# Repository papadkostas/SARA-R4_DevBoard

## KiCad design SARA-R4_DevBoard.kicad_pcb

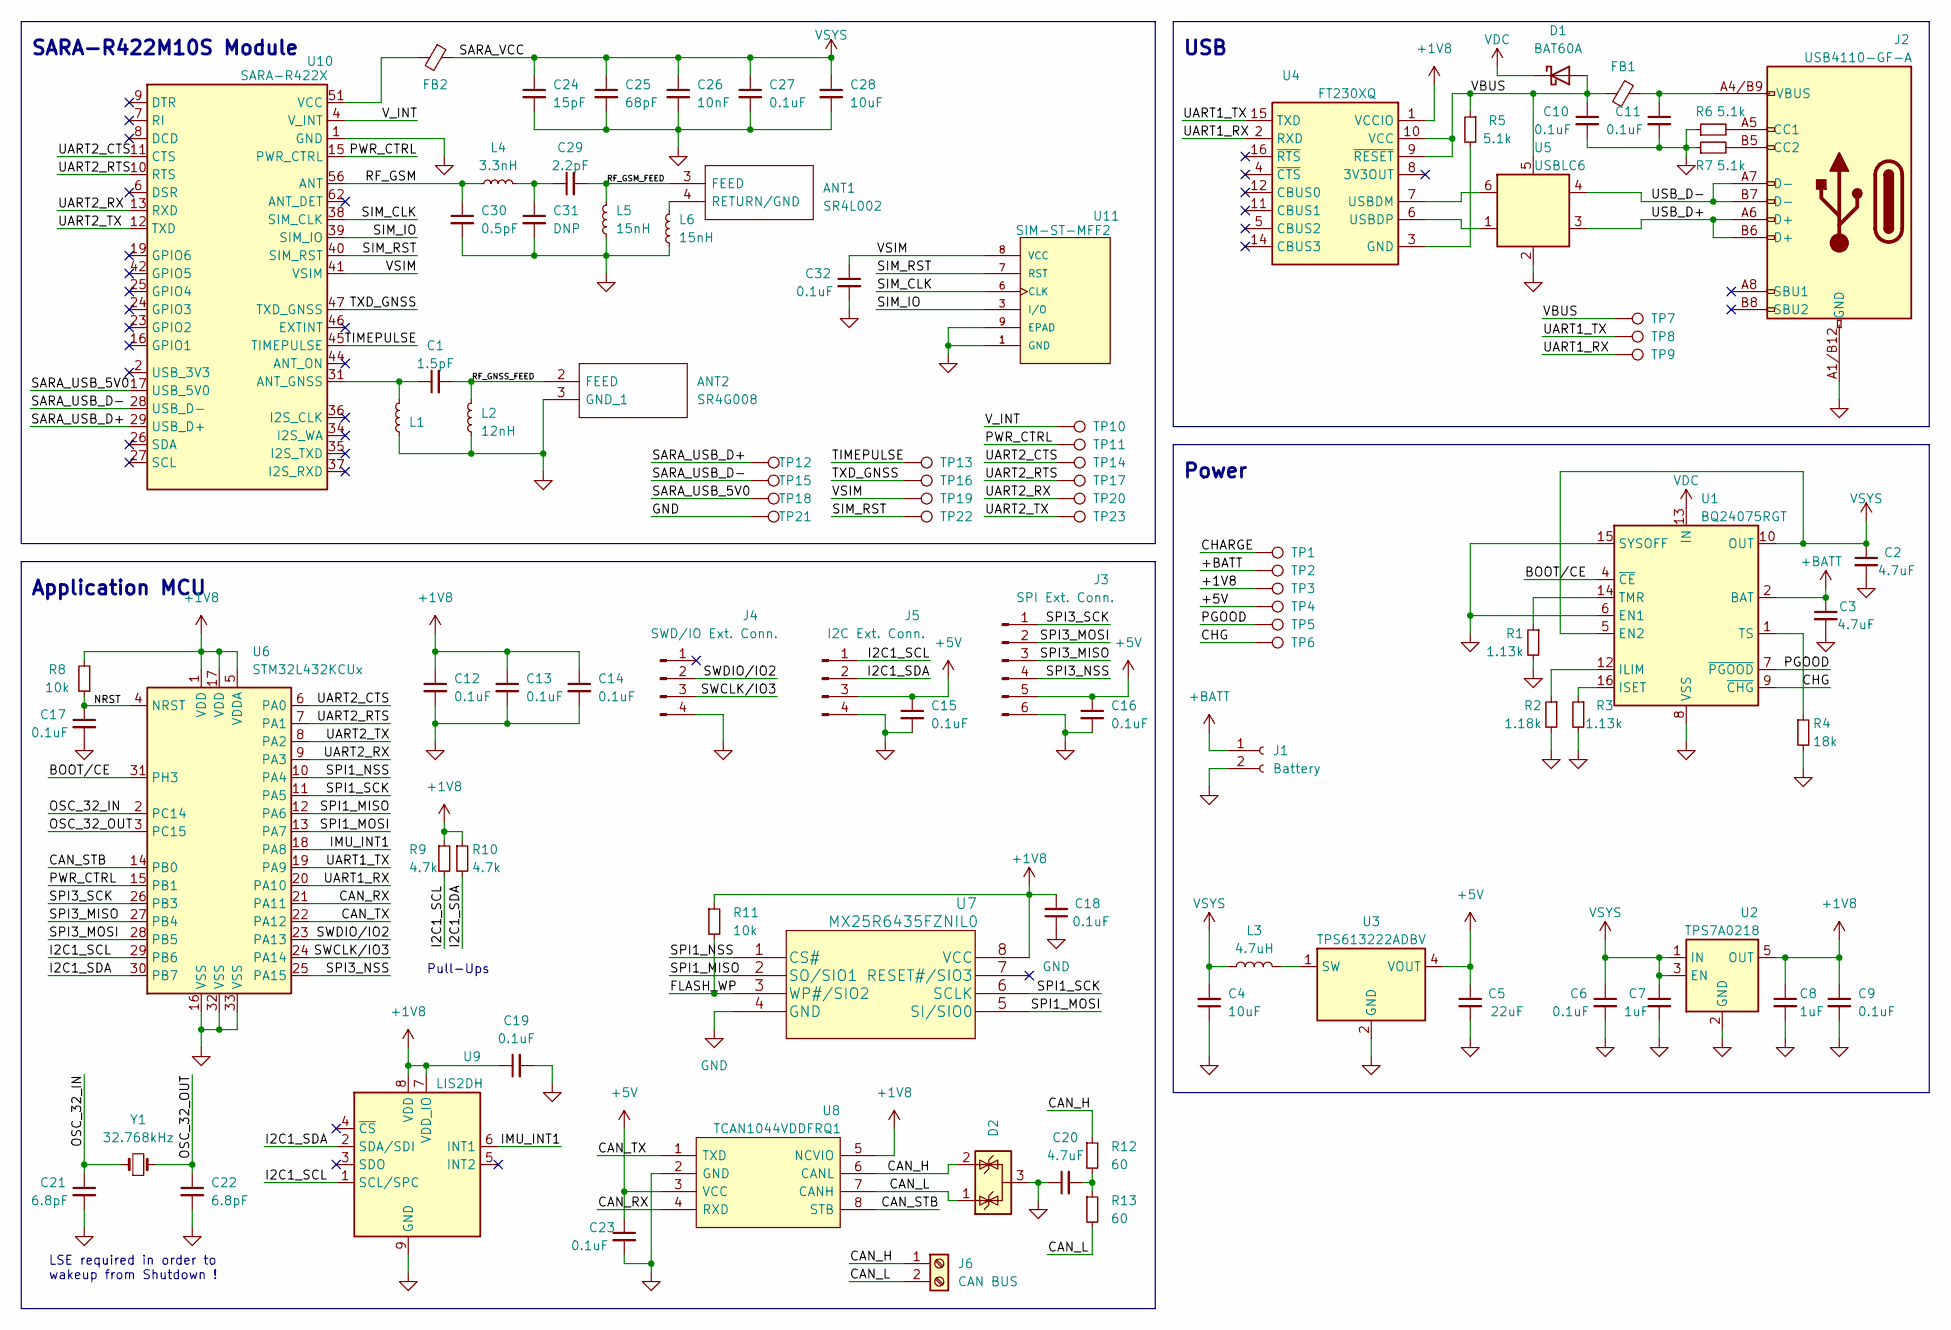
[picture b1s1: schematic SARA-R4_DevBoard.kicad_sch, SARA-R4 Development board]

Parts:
ANT1: SR4L002; Manufacturer_Part_Number SR4L002; Mouser Part Number 237-SR4L002
ANT2: SR4G008; Manufacturer_Part_Number SR4G008; Mouser Part Number 237-SR4G008
C1: 1.5pF; C_0402_1005Metric
C2, C3, C20: 4.7uF; C_0402_1005Metric
C4: 10uF; C_0402_1005Metric
C5: 22uF; C_0402_1005Metric
C6, C9, C10, C11, C12, C13, C14, C15, C16, C17, C18, C19, C23: 0.1uF; C_0402_1005Metric
C7, C8: 1uF; C_0402_1005Metric
C21, C22: 6.8pF; C_0402_1005Metric
C24: 15pF; C_0402_1005Metric; Part GRM1555C1H150J
C25: 68pF; C_0402_1005Metric; Part GRM1555C1H680J
C26: 10nF; C_0402_1005Metric; Part GRM155R71C103K
C27, C32: 0.1uF; C_0402_1005Metric; Part GRM155R61C104K
C28: 10uF; C_0402_1005Metric; Part T520B107M006ATE015
C29: 2.2pF; C_0402_1005Metric
C30: 0.5pF; C_0402_1005Metric
C31: DNP; C_0402_1005Metric
D1: BAT60A; D_SOD-323
D2: SZNUP2115LT1G; SOT-23
FB1: USB_Bead; L_0603_1608Metric
FB2: FerriteBead_Small; L_0603_1608Metric; Part BLM18EG221SN1
J1: Battery; JST_PH_S2B-PH-SM4-TB_1x02-1MP_P2.00mm_Horizontal
J2: USB4110-GF-A; GCT_USB4110-GF-A_REVB; Manufacturer_Part_Number USB4110-GF-A; Mouser Part Number 640-USB4110-GF-A
J3: SPI Ext. Conn.; JST_SH_SM06B-SRSS-TB_1x06-1MP_P1.00mm_Horizontal
J4: SWD/IO Ext. Conn.; JST_SH_SM04B-SRSS-TB_1x04-1MP_P1.00mm_Horizontal
J5: I2C Ext. Conn.; JST_SH_SM04B-SRSS-TB_1x04-1MP_P1.00mm_Horizontal
J6: CAN BUS; C_0603_1608Metric
L1: L_Small; L_0402_1005Metric
L2: 12nH; L_0402_1005Metric
L3: 4.7uH; L_0402_1005Metric
L4: 3.3nH; L_0402_1005Metric
L5, L6: 15nH; L_0402_1005Metric
R1, R3: 1.13k; R_0402_1005Metric
R2: 1.18k; R_0402_1005Metric
R4: 18k; R_0402_1005Metric
R5, R6, R7: 5.1k; R_0402_1005Metric
R8, R11: 10k; R_0402_1005Metric
R9, R10: 4.7k; R_0402_1005Metric
R12, R13: 60; R_0402_1005Metric
TP1: CHARGE; TestPoint_Pad_D1.0mm
TP2: BATT; TestPoint_Pad_D1.0mm
TP3: 1V8; TestPoint_Pad_D1.0mm
TP4, TP5, TP6: 5V; TestPoint_Pad_D1.0mm
TP7: VBUS; TestPoint_Pad_D1.0mm
TP8: UART1_TX; TestPoint_Pad_D1.0mm
TP9: UART1_RX; TestPoint_Pad_D1.0mm
TP10, TP11, TP13, TP14, TP16, TP17, TP19, TP20, TP22, TP23: TestPoint; TestPoint_Pad_D1.0mm
TP12: USB_D+; TestPoint_Pad_D1.0mm
TP15: USB_D-; TestPoint_Pad_D1.0mm
TP18, TP21: SARA_USB_5V0; TestPoint_Pad_D1.0mm
U1: BQ24075RGT; VQFN-16-1EP_3x3mm_P0.5mm_EP1.6x1.6mm
U2: TPS7A0218; SOT-23-5
U3: TPS613222ADBV; SOT-23-5
U4: FT230XQ; QFN-16-1EP_4x4mm_P0.65mm_EP2.1x2.1mm
U5: USBLC6; SOT-23-6
U6: STM32L432KCUx; QFN-32-1EP_5x5mm_P0.5mm_EP3.45x3.45mm
U7: MX25R6435FZNIL0; WSON-8-1EP_4x4mm_P0.8mm_EP2.2x3mm
U8: TCAN1044VDDFRQ1; SOT65P280X110-8N; Manufacturer_Part_Number TCAN1044VDDFRQ1; Mouser Part Number 595-TCAN1044VDDFRQ1
U9: LIS2DH; LGA-14_2x2mm_P0.35mm_LayoutBorder3x4y
U10: SARA-R422X; ublox_SARA-G3_LGA-96
U11: SIM-ST-MFF2; DFN-8-1EP_6x5mm_P1.27mm_EP4x4mm
Y1: 32.768kHz; NX3215SA32768KEXS00AMU00003

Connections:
+1V8: C8.1, C9.1, C12.1, C13.1, C14.1, C18.2, C19.1, R8.2, R9.1, R10.1, R11.1, TP3.1, U2.5 (OUT), U4.1 (VCCIO), U6.1 (VDD), U6.5 (VDDA), U6.17 (VDD), U7.8 (VCC), U8.5 (NCVIO), U9.7 (VDD_IO), U9.8 (VDD)
+5V: C5.1, C15.1, C16.1, C23.1, J3.5, J5.3, TP4.1, U3.4 (VOUT), U8.3 (VCC)
+BATT: C3.1, J1.1, U1.2 (BAT), U1.3 (BAT)
/BOOT/CE: U1.4 (~CE), U6.31 (PH3)
/CAN_H: D2.2 (K), J6.1, R12.1, U8.6 (CANL)
/CAN_L: D2.1 (K), J6.2, R13.2, U8.7 (CANH)
/CAN_RX: U6.21 (PA11), U8.4 (RXD)
/CAN_STB: U6.14 (PB0), U8.8 (STB)
/CAN_TX: U6.22 (PA12), U8.1 (TXD)
/CHG: TP6.1, U1.9 (~CHG)
/FLASH_WP: R11.2, U7.3 (WP#/SIO2)
/I2C1_SCL: J5.1, R9.2, U6.29 (PB6), U9.1 (SCL/SPC)
/I2C1_SDA: J5.2, R10.2, U6.30 (PB7), U9.2 (SDA/SDI)
/IMU_INT1: U6.18 (PA8), U9.6 (INT1)
/NRST: C17.1, R8.1, U6.4 (NRST)
/OSC_32_IN: C21.1, U6.2 (PC14), Y1.1
/OSC_32_OUT: C22.1, U6.3 (PC15), Y1.2
/PGOOD: TP5.1, U1.7 (~PGOOD)
/PWR_CTRL: TP11.1, U6.15 (PB1), U10.15 (PWR_CTRL)
/RF_GNSS_FEED: ANT2.2 (FEED), C1.2, L2.2
/RF_GSM: C30.1, L4.1, U10.56 (ANT)
/RF_GSM_FEED: ANT1.3 (FEED), C29.2, L5.2
/SARA_USB_5V0: TP18.1, U10.17 (USB_5V0)
/SARA_USB_D+: TP12.1, U10.29 (USB_D+)
/SARA_USB_D-: TP15.1, U10.28 (USB_D-)
/SIM_CLK: U10.38 (SIM_CLK), U11.6 (CLK)
/SIM_IO: U10.39 (SIM_IO), U11.3 (I/O)
/SIM_RST: TP22.1, U10.40 (SIM_RST), U11.7 (RST)
/SPI1_MISO: U6.12 (PA6), U7.2 (SO/SIO1)
/SPI1_MOSI: U6.13 (PA7), U7.5 (SI/SIO0)
/SPI1_NSS: U6.10 (PA4), U7.1 (CS#)
/SPI1_SCK: U6.11 (PA5), U7.6 (SCLK)
/SPI3_MISO: J3.3, U6.27 (PB4)
/SPI3_MOSI: J3.2, U6.28 (PB5)
/SPI3_NSS: J3.4, U6.25 (PA15)
/SPI3_SCK: J3.1, U6.26 (PB3)
/SWCLK/IO3: J4.3, U6.24 (PA14)
/SWDIO/IO2: J4.2, U6.23 (PA13)
/TIMEPULSE: TP13.1, U10.45 (TIMEPULSE)
/TXD_GNSS: TP16.1, U10.47 (TXD_GNSS)
/UART1_RX: TP9.1, U4.2 (RXD), U6.20 (PA10)
/UART1_TX: TP8.1, U4.15 (TXD), U6.19 (PA9)
/UART2_CTS: TP14.1, U6.6 (PA0), U10.11 (CTS)
/UART2_RTS: TP17.1, U6.7 (PA1), U10.10 (RTS)
/UART2_RX: TP20.1, U6.9 (PA3), U10.13 (RXD)
/UART2_TX: TP23.1, U6.8 (PA2), U10.12 (TXD)
/USB_D+: J2.A6 (D+), J2.B6 (D+), U5.3 (I/O2)
/USB_D-: J2.A7 (D-), J2.B7 (D-), U5.4 (I/O2)
/VBUS: C10.1, D1.2 (A), FB1.1, R5.1, TP7.1, U4.9 (~RESET), U4.10 (VCC), U5.5 (VBUS)
/VSIM: C32.1, TP19.1, U10.41 (VSIM), U11.8 (VCC)
/V_INT: TP10.1, U10.4 (V_INT)
unnamed: ANT1.4 (RETURN/GND), L6.2
unnamed: C11.1, FB1.2, J2.A4/B9 (VBUS), J2.B4/A9 (VBUS)
unnamed: C20.2, R12.2, R13.1
unnamed: C29.1, C31.1, L4.2
unnamed: J2.A5 (CC1), R6.2
unnamed: J2.B5 (CC2), R7.2
unnamed: R2.1, U1.12 (ILIM)
unnamed: R3.1, U1.16 (ISET)
unnamed: R1.1, U1.14 (TMR)
unnamed: R4.1, U1.1 (TS)
unnamed: L3.1, U3.1 (SW)
unnamed: U4.7 (USBDM), U5.6 (I/O1)
unnamed: U4.6 (USBDP), U5.1 (I/O1)
unnamed: C1.1, L1.2, U10.31 (ANT_GNSS)
VCC: FB2.2, U10.51 (VCC), U10.52 (VCC), U10.53 (VCC)
VDC: D1.1 (K), U1.13 (IN)
VSYS: C2.1, C4.2, C6.1, C7.1, C24.1, C25.1, C26.1, C27.1, C28.1, FB2.1, L3.2, U1.5 (EN2), U1.10 (OUT), U1.11 (OUT), U2.1 (IN), U2.3 (EN)

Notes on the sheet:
Power
Application MCU
Pull-Ups
USB
LSE required in order to wakeup from Shutdown !
SARA-R422M10S Module

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
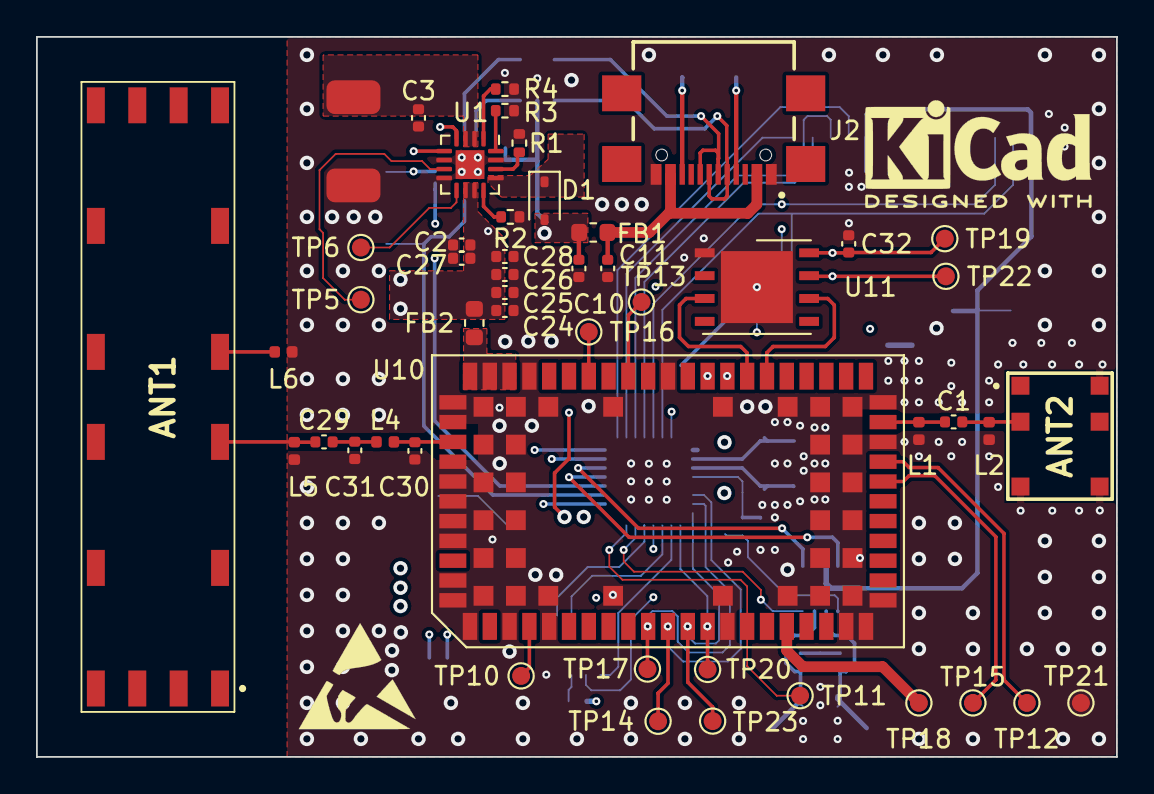
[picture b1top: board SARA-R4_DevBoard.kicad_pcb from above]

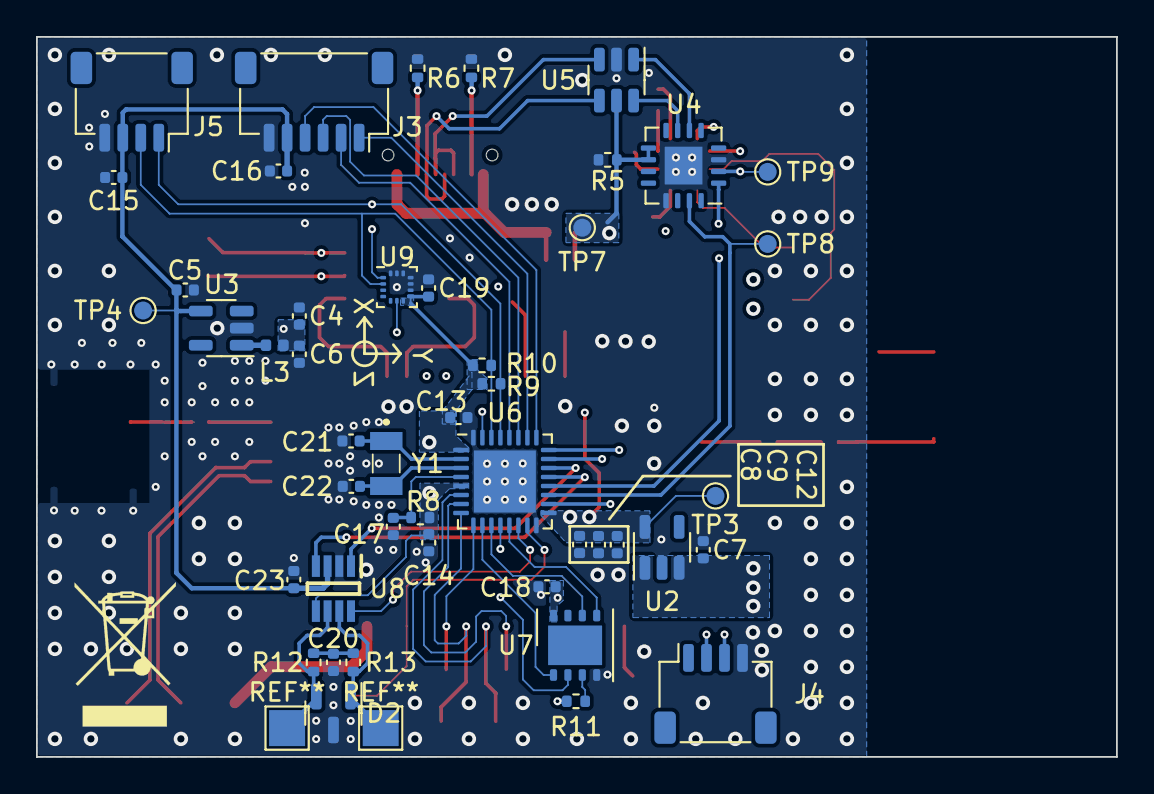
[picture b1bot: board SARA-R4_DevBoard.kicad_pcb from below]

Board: 4 copper layers, 60.0 x 40.0 mm, 95 parts (46 on the bottom side), 69 nets.

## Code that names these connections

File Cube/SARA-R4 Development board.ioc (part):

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Mcu.Name=STM32L432K(B-C)Ux
Mcu.Package=UFQFPN32
Mcu.UserName=STM32L432KCUx
PA0.Mode=CTS_RTS
PA0.Signal=USART2_CTS
PA1.Mode=CTS_RTS
PA1.Signal=USART2_RTS
PA10.Mode=Asynchronous
PA10.Signal=USART1_RX
PA13\ (JTMS-SWDIO).Mode=Serial_Wire
PA13\ (JTMS-SWDIO).Signal=SYS_JTMS-SWDIO
PA14\ (JTCK-SWCLK).Mode=Serial_Wire
PA14\ (JTCK-SWCLK).Signal=SYS_JTCK-SWCLK
PA15\ (JTDI).Mode=NSS_Signal_Hard_Output
PA15\ (JTDI).Signal=SPI3_NSS
PA2.Mode=Asynchronous
PA2.Signal=USART2_TX
PA3.Mode=Asynchronous
PA3.Signal=USART2_RX
PA4.Mode=NSS_Signal_Hard_Output
PA4.Signal=SPI1_NSS
PA5.Mode=Full_Duplex_Master
PA5.Signal=SPI1_SCK
PA6.Mode=Full_Duplex_Master
PA6.Signal=SPI1_MISO
PA7.Mode=Full_Duplex_Master
PA7.Signal=SPI1_MOSI
PA9.Mode=Asynchronous
PA9.Signal=USART1_TX
PB0.Signal=GPXTI0
PB1.Signal=GPXTI1
PB3\ (JTDO-TRACESWO).Mode=Full_Duplex_Master
PB3\ (JTDO-TRACESWO).Signal=SPI3_SCK
PB4\ (NJTRST).Mode=Full_Duplex_Master
PB4\ (NJTRST).Signal=SPI3_MISO
PB5.Mode=Full_Duplex_Master
PB5.Signal=SPI3_MOSI
PB6.Mode=I2C
PB6.Signal=I2C1_SCL
PB7.Mode=I2C
PB7.Signal=I2C1_SDA
PC14-OSC32_IN\ (PC14).Mode=LSE-External-Oscillator
PC14-OSC32_IN\ (PC14).Signal=RCC_OSC32_IN
PC15-OSC32_OUT\ (PC15).Mode=LSE-External-Oscillator
PC15-OSC32_OUT\ (PC15).Signal=RCC_OSC32_OUT
RCC.HSE_VALUE=8000000
board=custom

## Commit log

2023-03-08 Force update
2023-03-08 Add zipped gerbers
2023-03-08 Remove backups and update gerbers
